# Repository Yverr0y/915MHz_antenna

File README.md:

# 915 MHz Antenna Designs

A collection of PCB antenna designs for the AU925 ISM band (915-928 MHz), simulated in EMerge.

## PIFA (925 MHz)

Shorted-patch PIFA optimised for 925 MHz on a 2-layer 1.6 mm FR-4 PCB.

- **Patch**: 34.42 x 26.00 mm on F.Cu, shorted to GND via 6 plated-through vias
- **Feed**: Via offset 7.00 mm from the shorted edge
- **Board**: 100 x 80 mm, full B.Cu ground plane
- **Matching**: Pi network (L1, C1, C2) between SMA and antenna feed

### Simulation Results

| Metric | Value |
|--------|-------|
| Resonance | 925.0 MHz (-33.23 dB) |
| -10 dB BW | 920 - 930 MHz (10 MHz) |
| S11 at 925 MHz | -33.23 dB |
| S11 at 915 MHz | -7.09 dB |

See [`915MHz_PIFA/`](915MHz_PIFA/) for the full KiCad project, EMerge simulation scripts, and verification data.

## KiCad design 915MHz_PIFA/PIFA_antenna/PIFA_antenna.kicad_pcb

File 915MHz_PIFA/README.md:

# PIFA 925 MHz Test Board

Shorted-patch PIFA optimised for 925 MHz on a 2-layer 1.6 mm FR-4 PCB, simulated in EMerge.

## Design

- **Patch**: 34.42 x 26.00 mm on F.Cu, shorted to GND via 6 plated-through vias
- **Feed**: Via offset 7.00 mm from the shorted edge
- **Board**: 100 x 80 mm, full B.Cu ground plane
- **Matching**: Pi network (L1, C1, C2) between SMA and antenna feed
- **Connector**: SMA edge-mount (Amphenol 132289)

## Simulation Results

Verified 2026-04-12 with EMerge FEM, 700-1300 MHz sweep.

| Metric | Value |
|--------|-------|
| Resonance | 925.0 MHz (-33.23 dB) |
| -10 dB BW | 920 - 930 MHz (10 MHz) |
| S11 at 925 MHz | -33.23 dB |
| S11 at 915 MHz | -7.09 dB |

## Reproducing

```bash
cd 915MHz_PIFA
python verify.py
```

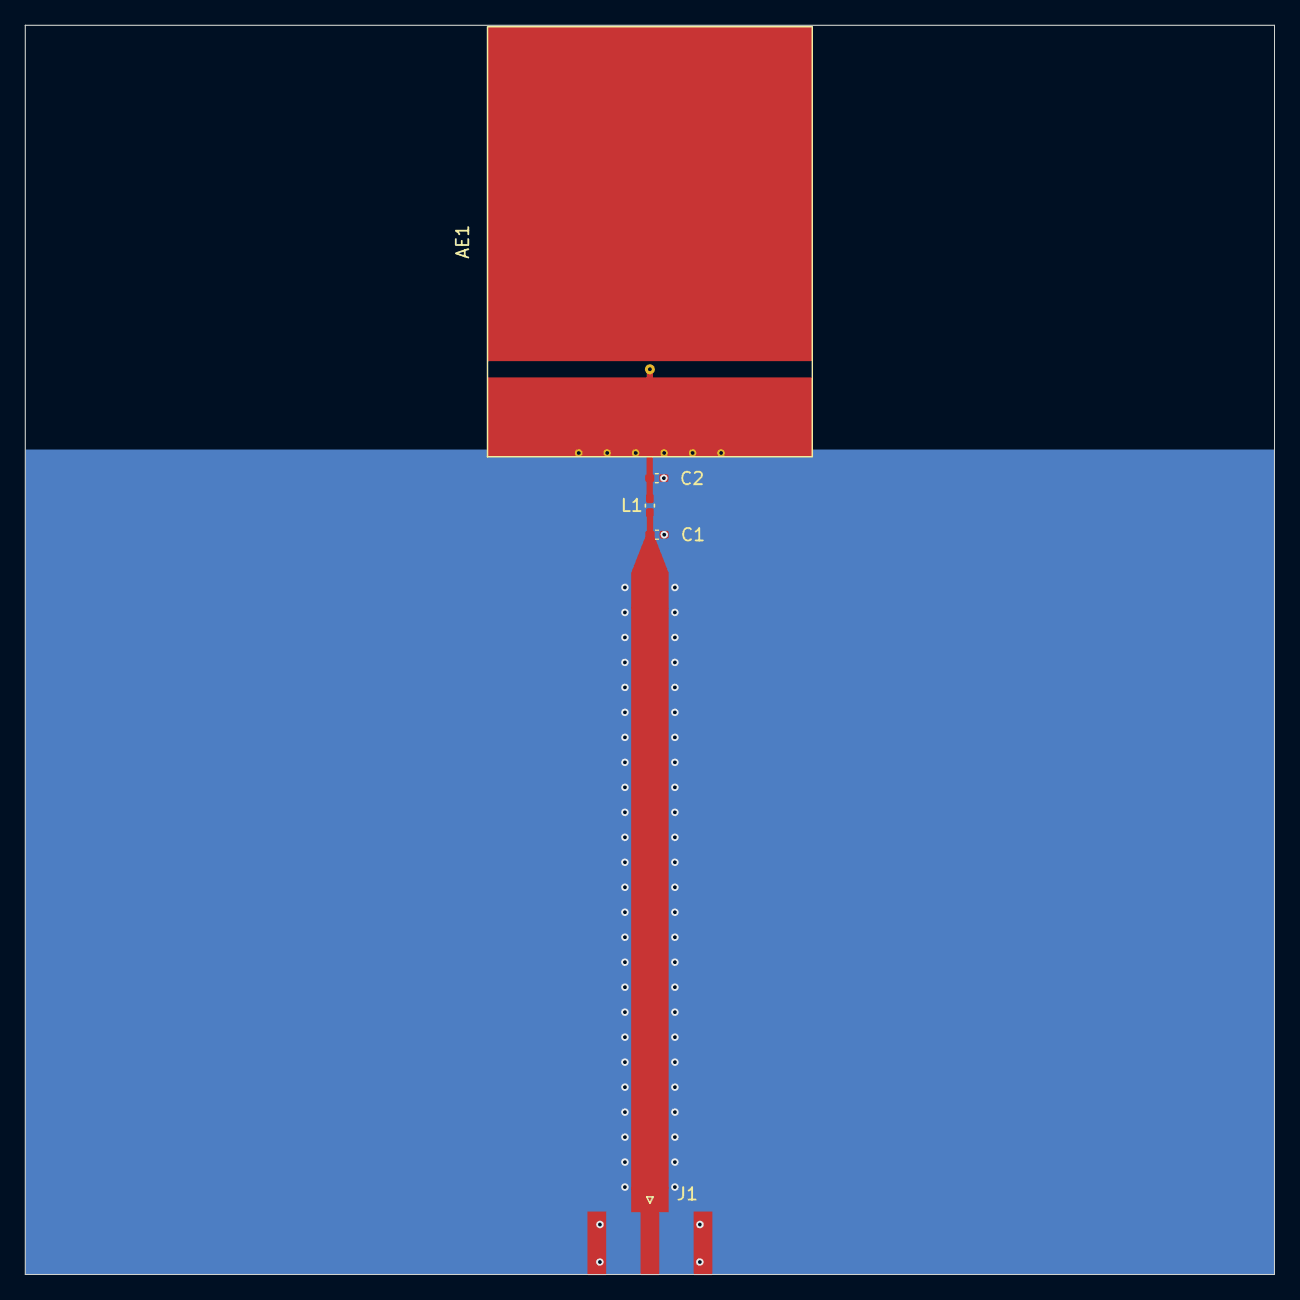
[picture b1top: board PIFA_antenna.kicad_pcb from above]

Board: 2 copper layers, 100.0 x 100.0 mm, 5 parts (0 on the bottom side), 3 nets.

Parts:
AE1: Antenna; PIFA_915_AU915
C1, C2: C; C_0402_1005Metric_Pad0.74x0.62mm_HandSolder
J1: Conn_Coaxial_Small; SMA_Amphenol_132289_EdgeMount
L1: L; C_0402_1005Metric_Pad0.74x0.62mm_HandSolder

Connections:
GND: AE1.1 (A), C1.2, C2.2, J1.2 (Ext)
unnamed: AE1.1 (A), AE1.2, C2.1, L1.2
unnamed: C1.1, J1.1 (In), L1.1

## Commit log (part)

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2026-03-05 moving files across
2026-04-12 Antenna
2026-04-12 readme added
2026-04-12 finalising report
2026-04-12 Modified for 925MHz
2026-04-12 fixed mangled smith chart
